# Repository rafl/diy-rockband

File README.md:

# A resource for playing Rock Band games in 2020

I'm using this repository to collect and share information vaguely related to
various ways of playing the Rock Band series of games from Harmonix on
different platforms and with different peripherals.

So far it mostly details what I know about the Mad Catz MIDI Pro Adapter, and
includes a hardware design and software to build custom game peripherals based
on either emulating the MIDI Pro Adapter or by interfacing with an existing
game peripherals.

I'm hoping to include more information on other peripherals as well as software
to emulate and/or interface with more of them in the future.

## Kudos

* (Wii) bookreader52 for patience in answering a lot of questions I had on legacy game controllers
* https://github.com/curiousjp for his Rock Band-related blog posts and open source MIDI Pro Emulation code for Teensy 3.6

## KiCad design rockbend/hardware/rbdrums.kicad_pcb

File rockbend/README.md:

# A DIY Rock Band MIDI Controller/Adapter

## Features:

* Ability to freely map MIDI events to controller inputs
* USB MIDI input, including support for high speed devices
* DIN 41524 MIDI input, allowing it to replace MIDI Pro adapters
* MIDI output via DIN and USB
* Native controller support, not requiring additional controllers to join and
  allowing system menus to be navigated
* Wireless support, eliminating the need for extremely long USB or MIDI cables

## Requirements:

* A native Rock Band drum controller for your platform
* A Teensy 4.0 (porting to other Teensy models or other micro controllers would be easy)
* An external DIN MIDI and/or USB MIDI Host I/O circuit
  * You can build one yourself based on the provided schematic, or use the provided PCB
* An optional enclosure
  * You can build one yourself, or use the provided 3d-printed one

## Firmware

The firmware uses the platformio.org ecosystem. You can build and upload it
using `pio run -t upload`.

There's real no configuration currently, and most behaviour is just hardcoded
in [main.cpp](firmware/src/main.cpp). You can change your MIDI mapping and
pinout by making changes there.

## Hardware

The [schematic](hardware/rbdrums.pdf) includes DIN MIDI input, DIN MIDI output,
and USB Host MIDI input. You can omit the ones you don't need as you see fit.

### Connecting to controller PCB

I've only used this with a PlayStation 4 drum wireless drum controller that
shipped with Rock Band 4.

The same approach will also work for other drum controllers, but might need
some software tweaks. You might however lose some features, such as being able
to natively navigate system menus on PS4 when using a PS3 drum controller.

Similarly, the same approach will also work with other platforms, such as Xbox
One, Xbox 360, and Wii, as long as you have an appropriate native drum kit for
that platform.

#### Drum Pads

The inputs for the drum pads are easily accessible on the controller PCB and
labeled with the corresponding color on the silk screen. I've re-used the JST
connectors that the piezo elements were connected to in the original drum
controller, but you can also solder to the test points next to the JST
connectors. Note that the polarity is flipped between the connectors on the
left and right side of the controller. Be sure to not accidentally flip signal
and ground.

#### Kick

This is accessible using a JST connector at the bottom of the controller PCB,
similar to the drum pad inputs.

#### Cymbals

These inputs are accessible via 5-pin JST connector at the top of the
controller PCB. The signals for the three cymbals are on the 3 center pins,
surrounded by GND and V+ on either side.

#### Buttons

These are optional and not required to just be able to play Rock Band drums,
but can be connected to the micro controller to allow the firmware to trigger
them, for example to be able to pause the game with a spare cymbal.
Additionally, triggering the 4 drum pads using these buttons as opposed to the
piezo sensor inputs seems to cause less latency within the original controller
firmware.

The inputs aren't broken out in an easily accessible way. I've connected the
signals to the "far" end of the current limiting resistors on each of the input
pins on the controller PCB.

#### Power

This is accessible as a JST header on the top right of the controller PCB.
Supplying 3.3V works fine, even though that's slightly higher than the
controller's original supply voltage. The 250mA provided by the Teensy's 3.3V
regulator are plenty to power the controller PCB.

You can use the Ground pin on the power connector or any of the signal
connectors or a combination thereof to reference to the Teensy's Ground.

### PCB

The provided [PCB](hardware/rbdrums.kicad_pcb) provides an easy way to connect
the Teensy to MIDI inputs and outputs as well as the appropriate places on the
controller PCB.

Please note that:

* You don't need to connect all the Ground pads provided. Any one will do. More
  than one won't hurt.

* Ground and Signal pads are swapped for two of the drum pad outputs to
  accommodate for the flipped polarity on two of the original JST connectors.

* Some mounting holes shouldn't be used, as they're too close to traces. Metal
  screws will damage those traces. Nylon screws might be OK to use for them,
  but you really don't need all of them.

* The 15kΩ pull-down resistance for USB D+ and D- is split into 2 resistors in
  series each, as I didn't have 15kΩ resistors handy. If you do, just use one
  resistor each accross the two footprints.

* There should probably be some input protection for the DIN MIDI output. Don't
  accidentally plug your instrument's MIDI output into the controller's MIDI
  output.

### Enclosure

The provided 3d-printed [enclosure](enclosure/) isn't great, but works well
enough. You'll need some M3 nuts and bolts for assembly. There's embedded
cutouts for M3 hex nuts to attach the front panel to the rest of the box.
You'll need to pause the print at the appropriate layer to insert these hex
nuts before continuing.

The design is available at
https://cad.onshape.com/documents/a9620f856c6ff58f2b23ec93/w/108910e108c10d455aeabe6d/e/1614ddb50d750c8a54a42bdd

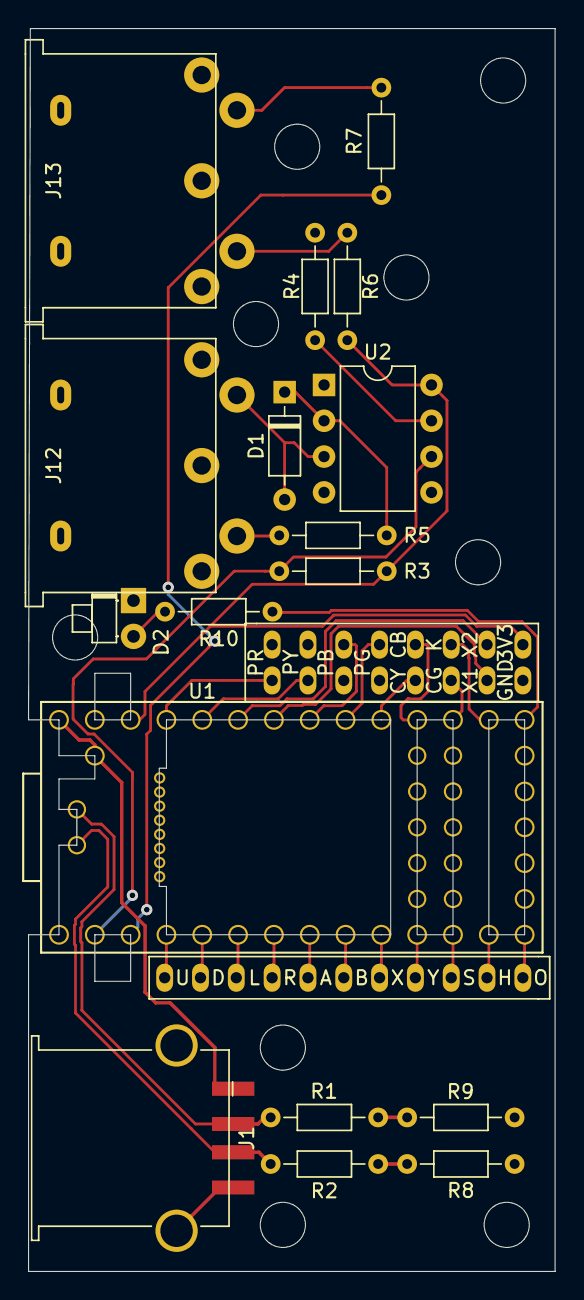
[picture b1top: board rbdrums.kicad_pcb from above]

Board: 2 copper layers, 37.3 x 88.1 mm, 28 parts (0 on the bottom side), 38 nets.

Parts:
D1: 1N914; D_DO-35_SOD27_P7.62mm_Horizontal
D2: LED; LED_D1.8mm_W1.8mm_H2.4mm_Horizontal_O1.27mm_Z1.6mm
H1, H2, H3, H4, H5, H6, H7, H8, H9: MountingHole; MountingHole_3.2mm_M3_ISO14580
J1: USB_A; USB_A_Stewart_SS-52100-001_Horizontal
J2: Conn_02x08_Odd_Even; pad_connector
J10: Conn_01x11_Male; ui_connector
J12, J13: DIN-5_180degree; DIN5-180Deg-Female-MIDI
R1, R2: 10k; R_Axial_DIN0204_L3.6mm_D1.6mm_P7.62mm_Horizontal
R3: 470; R_Axial_DIN0204_L3.6mm_D1.6mm_P7.62mm_Horizontal
R4, R8, R9: 4.7k; R_Axial_DIN0204_L3.6mm_D1.6mm_P7.62mm_Horizontal
R5: 220; R_Axial_DIN0204_L3.6mm_D1.6mm_P7.62mm_Horizontal
R6, R7: 47; R_Axial_DIN0204_L3.6mm_D1.6mm_P7.62mm_Horizontal
R10: R; R_Axial_DIN0204_L3.6mm_D1.6mm_P7.62mm_Horizontal
U1: Teensy4.0; Teensy40_SMT
U2: 6N138; DIP-8_W7.62mm

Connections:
+3V3: J2.16, R3.1, R6.1, U1.31, U2.8
D+: J1.3, R2.1, U1.54
D-: J1.2, R1.1, U1.53
GND: D2.1, J1.4, J1.5, J2.2, J2.4, J2.5, J2.7, J2.15, J13.2, J13.S, R4.2, R8.1, R9.1, U1.1, U1.17, U1.32, U2.5
IN_MIDI: R3.2, U1.2, U2.6
LED1: R10.1, U1.20
unnamed: D1.1, R5.2, U2.2
unnamed: D1.2, J12.5, U2.3
unnamed: D2.2, R10.2
unnamed: J12.4, R5.1
unnamed: J13.4, R6.2
unnamed: J13.5, R7.2
unnamed: R1.2, R9.2
unnamed: R2.2, R8.2
unnamed: R4.1, U2.7
OUT_A: J10.5, U1.8
OUT_AUX1: J2.13, U1.27
OUT_AUX2: J2.14, U1.28
OUT_B: J10.6, U1.9
OUT_CYM_BLUE: J2.10, U1.23
OUT_CYM_GREEN: J2.11, U1.22
OUT_CYM_YELLOW: J2.9, U1.24
OUT_DOWN: J10.2, U1.5
OUT_HOME: J10.10, U1.13
OUT_KICK: J2.12, U1.21
OUT_LEFT: J10.3, U1.6
OUT_MIDI: R7.1, U1.3
OUT_OPTIONS: J10.11, U1.14
OUT_PAD_BLUE: J2.6, U1.26
OUT_PAD_GREEN: J2.8, U1.25
OUT_PAD_RED: J2.1, U1.30
OUT_PAD_YELLOW: J2.3, U1.29
OUT_RIGHT: J10.4, U1.7
OUT_SHARE: J10.9, U1.12
OUT_UP: J10.1, U1.4
OUT_X: J10.7, U1.10
OUT_Y: J10.8, U1.11
VBUS: J1.1, U1.33, U1.34

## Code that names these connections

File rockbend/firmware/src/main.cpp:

#define _TASK_MICRO_RES
#include <TaskScheduler.h>
#include <USBHost_t36.h>
#include <MIDI.h>

#pragma GCC diagnostic error "-Wextra"

#define BIGBUFFER 1
#define DEBUG 1

#if BIGBUFFER
#  define MIDIDevice_t MIDIDevice_BigBuffer
#else
#  define MIDIDevice_t MIDIDevice
#endif

#if DEBUG
#  define DEB_SERIAL Serial
#  define DEB(...) DEB_SERIAL.printf(__VA_ARGS__)
#  define DEBP
#else
#  define DEB(...)
#  define DEBP __attribute__((unused))
#endif

typedef enum {
  OUT_KICK,
  OUT_PAD_RED,
  OUT_PAD_YELLOW,
  OUT_PAD_BLUE,
  OUT_PAD_GREEN,
  OUT_CYM_YELLOW,
  OUT_CYM_BLUE,
  OUT_CYM_GREEN,
  OUT_BUT_UP,
  OUT_BUT_DOWN,
  OUT_BUT_LEFT,
  OUT_BUT_RIGHT,
  OUT_BUT_A,
  OUT_BUT_B,
  OUT_BUT_X,
  OUT_BUT_Y,
  OUT_BUT_SHARE,
  OUT_BUT_HOME,
  OUT_BUT_OPTIONS,
  NUM_OUT,
} output_t;

#if DEBUG
static const char* const outputNames[NUM_OUT] = {
  "KICK",
  "PAD_RED",
  "PAD_YELLOW",
  "PAD_BLUE",
  "PAD_GREEN",
  "CYM_YELLOW",
  "CYM_BLUE",
  "CYM_GREEN",
  "BUT_UP",
  "BUT_DOWN",
  "BUT_LEFT",
  "BUT_RIGHT",
  "BUT_A",
  "BUT_B",
  "BUT_X",
  "BUT_Y",
  "BUT_SHARE",
  "BUT_HOME",
  "BUT_OPTIONS",
};
#endif

typedef struct {
  const unsigned long hold, holdOff;
} output_timing_t;

static const output_timing_t kickTiming = { .hold = 60 * TASK_MILLISECOND, .holdOff = 50 * TASK_MILLISECOND };
static const output_timing_t padTiming  = { .hold =  1 * TASK_MILLISECOND, .holdOff = 40 * TASK_MILLISECOND };
static const output_timing_t cymTiming  = { .hold = 25 * TASK_MILLISECOND, .holdOff = 40 * TASK_MILLISECOND };
static const output_timing_t butTiming  = { .hold = 25 * TASK_MILLISECOND, .holdOff = 40 * TASK_MILLISECOND };

typedef struct {
  const int pin;
  const output_timing_t *timing;
} output_conf_t;

#if __has_include("custom_kit.h")
#  include "custom_kit.h"
#else
static const output_conf_t outputs[NUM_OUT] = {
  [OUT_KICK]        = { .pin = 14, .timing = &kickTiming },
  [OUT_PAD_RED]     = { .pin = 23, .timing = &padTiming  },
  [OUT_PAD_YELLOW]  = { .pin = 22, .timing = &padTiming  },
  [OUT_PAD_BLUE]    = { .pin = 19, .timing = &padTiming  },
  [OUT_PAD_GREEN]   = { .pin = 18, .timing = &padTiming  },
  [OUT_CYM_YELLOW]  = { .pin = 15, .timing = &cymTiming  },
  [OUT_CYM_BLUE]    = { .pin = 16, .timing = &cymTiming  },
  [OUT_CYM_GREEN]   = { .pin = 17, .timing = &cymTiming  },
  [OUT_BUT_UP]      = { .pin =  2, .timing = &butTiming  },
  [OUT_BUT_DOWN]    = { .pin =  3, .timing = &butTiming  },
  [OUT_BUT_LEFT]    = { .pin =  4, .timing = &butTiming  },
  [OUT_BUT_RIGHT]   = { .pin =  5, .timing = &butTiming  },
  [OUT_BUT_A]       = { .pin =  6, .timing = &butTiming  },
  [OUT_BUT_B]       = { .pin =  7, .timing = &butTiming  },
  [OUT_BUT_X]       = { .pin =  8, .timing = &butTiming  },
  [OUT_BUT_Y]       = { .pin =  9, .timing = &butTiming  },
  [OUT_BUT_SHARE]   = { .pin = 10, .timing = &butTiming  },
  [OUT_BUT_HOME]    = { .pin = 11, .timing = &butTiming  },
  [OUT_BUT_OPTIONS] = { .pin = 12, .timing = &butTiming  },
};
#endif

typedef struct {
  unsigned long triggeredAt;
  bool triggered;
} output_state_t;

static output_state_t outputStates[NUM_OUT];

static const struct {
  const uint8_t hhHystLo, hhHystHi;
} input_conf = {
  .hhHystLo = 40,
  .hhHystHi = 90,
};

typedef enum {
  HH_OPEN,
  HH_CLOSED,
} hh_state_t;

static struct {
  hh_state_t hhState;
  bool hhSwitchEnable;
} input_state = {
  .hhState = HH_CLOSED,
  .hhSwitchEnable = true,
};

// this works reasonably well, but could use some refinement. maybe keep a
// buffer of recent notes instead. that way we could turn flams and such into
// R+Y hits and so on. maybe consider velocity, too. turning this into mostly
// configuration data might be nice, also.
static bool outputForNote(uint8_t note, output_t &out) {
  switch (note) {
    case 36:
      out = OUT_KICK;
      break;
    case 38:
    case 40:
      out = OUT_PAD_RED;
      break;
    case 43:
      out = OUT_PAD_GREEN;
      break;
    case 45:
      out = OUT_PAD_BLUE;
      break;
    case 26:
    case 46:
      out = !input_state.hhSwitchEnable || input_state.hhState == HH_CLOSED ? OUT_CYM_YELLOW : OUT_CYM_BLUE;
      break;
    case 48:
      out = OUT_PAD_YELLOW;
      break;
    case 49:
    case 52:
    case 55:
    case 57:
      out = OUT_CYM_GREEN;
      break;
    case 51:
    case 53:
    case 59:
      out = OUT_CYM_BLUE;
      break;
    case 41:
      input_state.hhSwitchEnable = !input_state.hhSwitchEnable;
      return false;
      break;
    default:
      return false;
  }
  return true;
}

static void writeOutput(output_t out, bool state) {
  digitalWrite(outputs[out].pin, state);
  outputStates[out].triggered = state;
}

static void noteOn(DEBP uint8_t channel, uint8_t note, DEBP uint8_t velocity) {
  DEB("%d %d %d ", channel, note, velocity);
  output_t out;
  if (!outputForNote(note, out)) {
    DEB("\n");
    return;
  }
  DEB("%s\n", outputNames[out]);

  auto io = &outputs[out];
  auto st = &outputStates[out];
  auto t = micros();
  if (t - st->triggeredAt > io->timing->hold + io->timing->holdOff) {
    writeOutput(out, HIGH);
    st->triggeredAt = t;
  }
}

static void cc(uint8_t, uint8_t control, uint8_t value) {
  if (control != 1 /* modulation wheel / HH pedal */) {
    return;
  }

  if (input_state.hhState == HH_OPEN && value >= input_conf.hhHystHi) {
    input_state.hhState = HH_CLOSED;
  }
  else if (input_state.hhState == HH_CLOSED && value <= input_conf.hhHystLo) {
    input_state.hhState = HH_OPEN;
  }
}

static USBHost usb;
static MIDIDevice_t usbMidi(usb);
static midi::MidiInterface<HardwareSerial> serialMidi(Serial1);

void setup() {
#if DEBUG
  DEB_SERIAL.begin(115200);
#endif

  for (auto out = 0; out < NUM_OUT; out++) {
    pinMode(outputs[out].pin, OUTPUT);
    writeOutput((output_t)out, LOW);
  }

  usb.begin();
  usbMidi.setHandleNoteOn(noteOn);
  usbMidi.setHandleControlChange(cc);

  serialMidi.begin(MIDI_CHANNEL_OMNI);
  serialMidi.setHandleNoteOn(noteOn);
  serialMidi.setHandleControlChange(cc);
}

static void runUsbMidiTask() {
  while (usbMidi.read()) {
    serialMidi.send(
      (midi::MidiType)usbMidi.getType(),
      usbMidi.getData1(),
      usbMidi.getData2(),
      usbMidi.getChannel()
    );
  }
}

static void runSerialMidiTask() {
  while (serialMidi.read()) {
    usbMidi.send(
      serialMidi.getType(),
      serialMidi.getData1(),
      serialMidi.getData2(),
      serialMidi.getChannel()
    );
  }
}

static void runTriggerTask() {
  auto t = micros();
  for (auto out = 0; out < NUM_OUT; out++) {
    if (outputStates[out].triggered && t - outputStates[out].triggeredAt > outputs[out].timing->hold) {
      writeOutput((output_t)out, LOW);
    }
  }
}

static Scheduler scheduler;
static Task usbTask(10, TASK_FOREVER, usb.Task, &scheduler, true);
static Task usbMidiTask(10, TASK_FOREVER, &runUsbMidiTask, &scheduler, true);
static Task serialMidiTask(10, TASK_FOREVER, &runSerialMidiTask, &scheduler, true);
static Task outputTask(10, TASK_FOREVER, &runTriggerTask, &scheduler, true);

void loop() {
  scheduler.execute();
}

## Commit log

2020-04-18 Add MIDI Pro Adapter schematic
2020-04-18 Document some observations
2020-04-18 Add firmware
2020-04-18 Add hardware
2020-04-18 List some MIDI Pro Adapter emulators
2020-04-18 Add a README
2020-04-18 Add a test application for emulating MIDI Pro Adapters
2020-04-18 Add framework-arduinoteensy-1.151.0
    https://dl.bintray.com/platformio/dl-packages/:framework-arduinoteensy-1.151.0.tar.gz
2020-04-18 Add software license
2020-04-18 Add hardware license
